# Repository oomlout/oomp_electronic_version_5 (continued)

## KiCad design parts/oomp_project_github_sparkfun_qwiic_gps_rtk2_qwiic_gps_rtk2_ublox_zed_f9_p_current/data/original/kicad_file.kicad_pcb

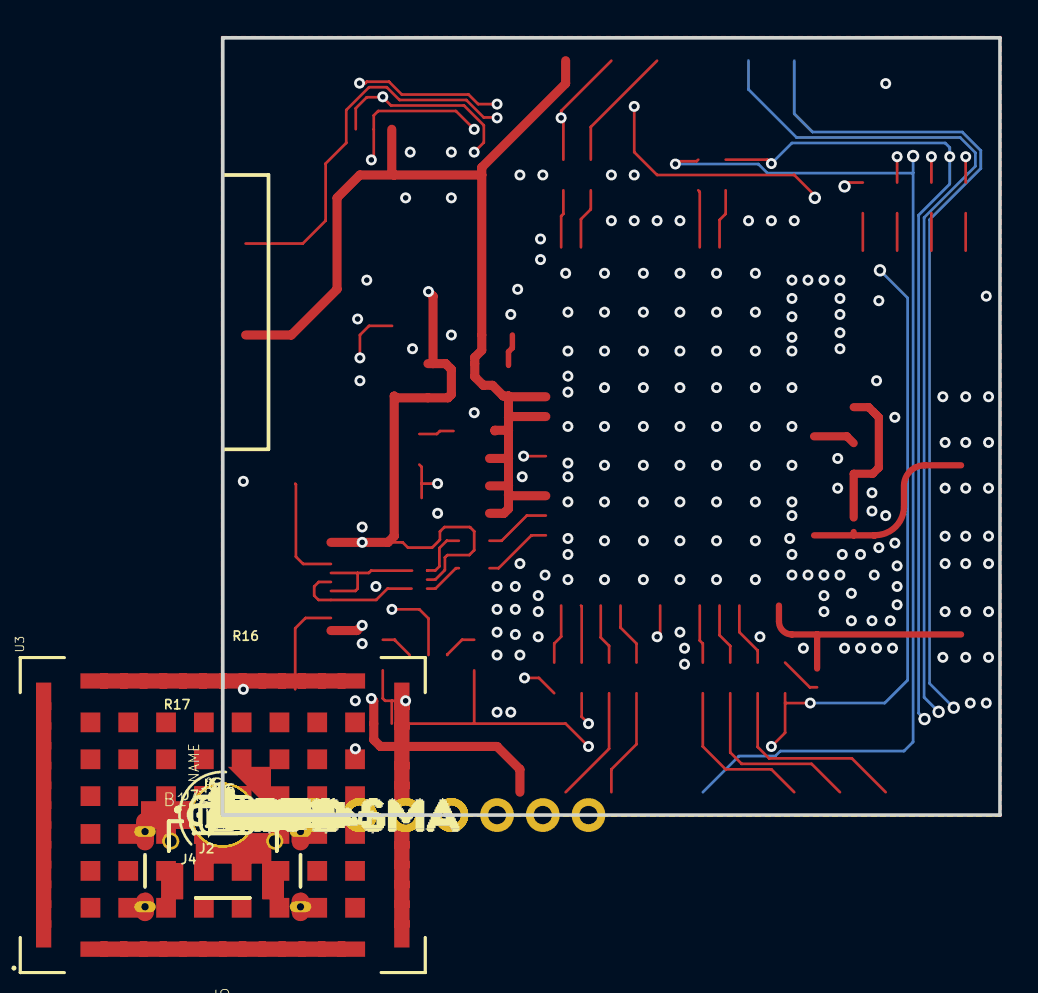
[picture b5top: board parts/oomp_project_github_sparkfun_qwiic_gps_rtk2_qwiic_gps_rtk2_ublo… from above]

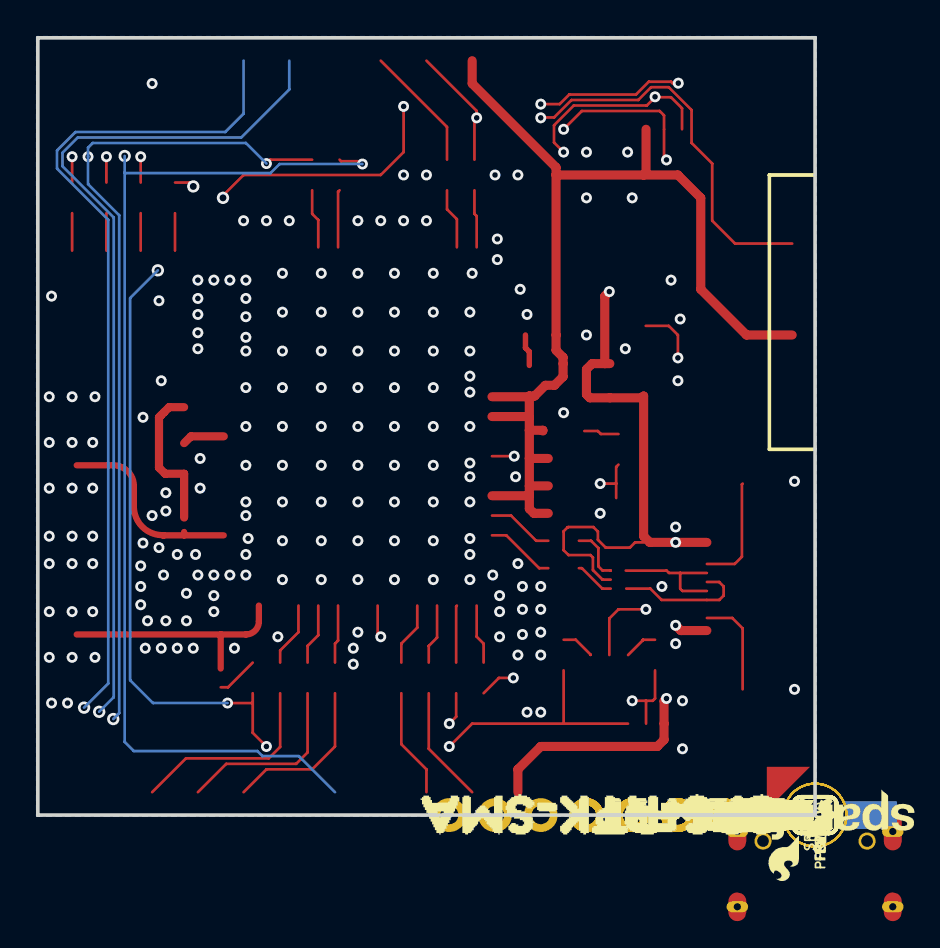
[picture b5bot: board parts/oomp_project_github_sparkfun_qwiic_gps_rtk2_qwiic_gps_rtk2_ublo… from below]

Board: 4 copper layers, 43.2 x 43.2 mm, 143 parts (44 on the bottom side), 52 nets.

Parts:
B1: 6.8MM_COIN_CELL; ML414H_IV01E
C1: 47pF; 0402
C2, C3, C4, C6: 1.0uF; 0603
C5, C7: 0.1uF; 0603
D1: Yellow; LED-0603
D2: 0.5A/40V/420mV; SOD-323
D3: GREEN; LED-0603
D4: BLUE; LED-0603
D6: PRTR5V0U2F; SOT886
E1, E2: SMA; SMA-EDGE
FB1: 120NH; 0402_MURATA
FENCE0: SMT-JUMPER_2_NC_TRACE_SILK
FRAME2: FRAME-LEDGER; CREATIVE_COMMONS
J1: Radio; 1X06_NO_SILK
J2, J4: Qwiic Right Angle; JST04_1MM_RA
J3: PTH; 1X04_NO_SILK
J5: USB-C-16P-2LAYER-PADS
J6: 1X06_NO_SILK
J7: 1X09_NO_SILK
JP5: SMT-JUMPER_3_2-NC_TRACE_SILK
JP21, JP61, JP71, JP81: FIDUCIALUFIDUCIAL; MICRO-FIDUCIAL
JP31, JP41, JP91, JP101: STAND-OFF
LED2: RED; LED-0603
LOGO1: OSHW-LOGOMINI; OSHW-LOGO-MINI
LOGO2: SFE_LOGO_NAME_FLAME.1_INCH; SFE_LOGO_NAME_FLAME_.1
PPS0: SMT-JUMPER_2_NC_TRACE_SILK
PPS_LED0: SMT-JUMPER_2_NC_TRACE_SILK
PWR0: SMT-JUMPER_2_NC_TRACE_SILK
R1, R5, R11, R12, R13: 1k; 0603
R2, R3, R4, R6, R14, R18, R19, R20, R21, R22, R23, R24, R25: 33; 0603
R7, R8: 2.2k; 0603
R9, R10: 27; 0603
R15: 100k; 0603
R16, R17: 5.1k; 0603
RTK0: SMT-JUMPER_2_NC_TRACE_SILK
SPI0: SMT-JUMPER_2_NO_SILK
U2: 3.3V; SOT23-5
U3: ZED-F9P
U$1, U$4: SDA-[)
U$2: SPECIAL_INSTRUCTIONS-ORDERING; ORDERING_INSTRUCTIONS
U$3, U$5: SCL-[)
U$6, U$7, U$60, U$61, U$66, U$67: 3V3-04
U$8, U$9, U$62, U$63: GND-04
U$10: I_SUPER2_C-()-03
U$11, U$54: FENCE2
U$12, U$18: PWR-()-03
U$13, U$28, U$29, U$32: RTK1
U$14, U$17: FENCE0
U$15, U$16: INT8
U$19, U$20: 5V
U$21, U$56, U$58: RX20
U$22: U#BLOX3
U$23, U$24: CS#-_]
U$25, U$52, U$72: PPS0
U$26, U$31: RX#MOSI3
U$27: DSEL0
U$30: QWIIC_4MM
U$33: SFE_LOGO_FLAME_.1
U$34, U$37: TX#MISO1
U$35, U$36: #RST3
U$38, U$41: SCK-(]-04
U$39, U$40: #SAFE1
U$42: RX22
U$43, U$44: PPS5
U$45, U$68: GND3
U$47, U$74: PPS1
U$48, U$70: RTCM5
U$49: ZED#F9P6
U$50, U$55, U$57: TX21
U$51: TX23
U$53, U$69: CORRECTION0
U$59: GPS0
U$65: ACTIVE_L1#L21
U$71, U$75: ANTENNA2
U$73: RTK#SMA4
U$76: GPS#RTK#SMA5

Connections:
3.3V: C2.1, C4.1, C5.2, C7.2, D2.A, J1.4, J2.2, J3.2, J4.2, J7.7, JP5.2, PWR0.2, R15.2, U2.5, U3.33, U3.34, U3.38
5V: C6.1, D6.5, J5.VBUS1, J5.VBUS2, J7.8, U2.1, U2.3
ANT_VCC: C1.1, FB1.P2, R14.1
BACKUP: B1.+, C3.1, R5.1, U3.36
CC1: J5.A5, R17.2
CC2: J5.B5, R16.2
D+: D6.4, R9.1
D-: D6.6, R10.1
D_SEL: SPI0.2, U3.47
FENCE_STAT: FENCE0.2, J6.1, R25.2
GND: B1.-, C1.2, C2.2, C3.2, C4.2, C5.1, C6.2, C7.1, D1.C, D3.C, D4.C, D6.2, E1.GND@0, E1.GND@1, E1.GND@2, E1.GND@3, E2.GND@0, E2.GND@1, E2.GND@2, E2.GND@3, J1.6, J2.1, J3.1, J4.1, J5.GND, J5.GND2, J5.SHLD1, J5.SHLD2, J5.SHLD3, J5.SHLD4, J7.9, LED2.C, R15.1, R16.1, R17.1, SPI0.1, U2.2, U3.1, U3.3, U3.12, U3.14, U3.32, U3.37, U3.41, U3.48, U3.55, U3.56, U3.57, U3.58, U3.59, U3.60, U3.61, U3.62, U3.63, U3.64, U3.65, U3.66, U3.67, U3.68, U3.69, U3.70, U3.71, U3.72, U3.73, U3.74, U3.75, U3.76, U3.77, U3.78, U3.79, U3.80, U3.81, U3.82, U3.83, U3.84, U3.85, U3.86, U3.87, U3.88, U3.89, U3.90, U3.91, U3.92, U3.93, U3.94, U3.95, U3.96, U3.97, U3.98, U3.99, U3.100, U3.101, U3.102
GPS_ANT1: E1.SIG, FB1.P1, U3.2
INT: J6.6, R18.2
unnamed: D3.A, R12.1
unnamed: D1.A, R11.1
unnamed: R12.2, RTK0.1
unnamed: PPS_LED0.1, R11.2
unnamed: JP5.1, R8.2
unnamed: D2.C, R5.2
unnamed: D4.A, R13.1
unnamed: JP5.3, R7.2
unnamed: FENCE0.1, R13.2
unnamed: LED2.A, R1.1
unnamed: R9.2, U3.40
unnamed: R10.2, U3.39
unnamed: R14.2, U3.7
unnamed: R22.1, U3.26
unnamed: R18.1, U3.51
unnamed: R19.1, U3.49
unnamed: PWR0.1, R1.2
unnamed: R20.1, U3.50
unnamed: R24.1, U3.20
unnamed: R25.1, U3.19
unnamed: PPS0.1, R21.1
PPS: E2.SIG, PPS0.2, U3.53
PPS_STAT: J6.3, PPS_LED0.2, R21.2
RTK_STAT: J6.2, R24.2, RTK0.2
RX2: J1.3, J7.5, R22.2
RXI/MOSI: J7.3, R6.2
RXLV: R6.1, U3.43
SCL/SCK: J2.4, J3.4, J4.4, J7.1, R4.2, R7.1
SCL_LV: R4.1, U3.45
SDA/~CS: J2.3, J3.3, J4.3, J7.4, R2.2, R8.1
SDA_LV: R2.1, U3.44
TX2: J1.2, J7.6, R23.2
TX2_P: R23.1, U3.27
TXLV: R3.1, U3.42
TXO/MISO: J7.2, R3.2
UNP_D+: D6.3, J5.A6, J5.B6
UNP_D-: D6.1, J5.A7, J5.B7
~RESET: J6.4, R19.2
~SAFE: J6.5, R20.2

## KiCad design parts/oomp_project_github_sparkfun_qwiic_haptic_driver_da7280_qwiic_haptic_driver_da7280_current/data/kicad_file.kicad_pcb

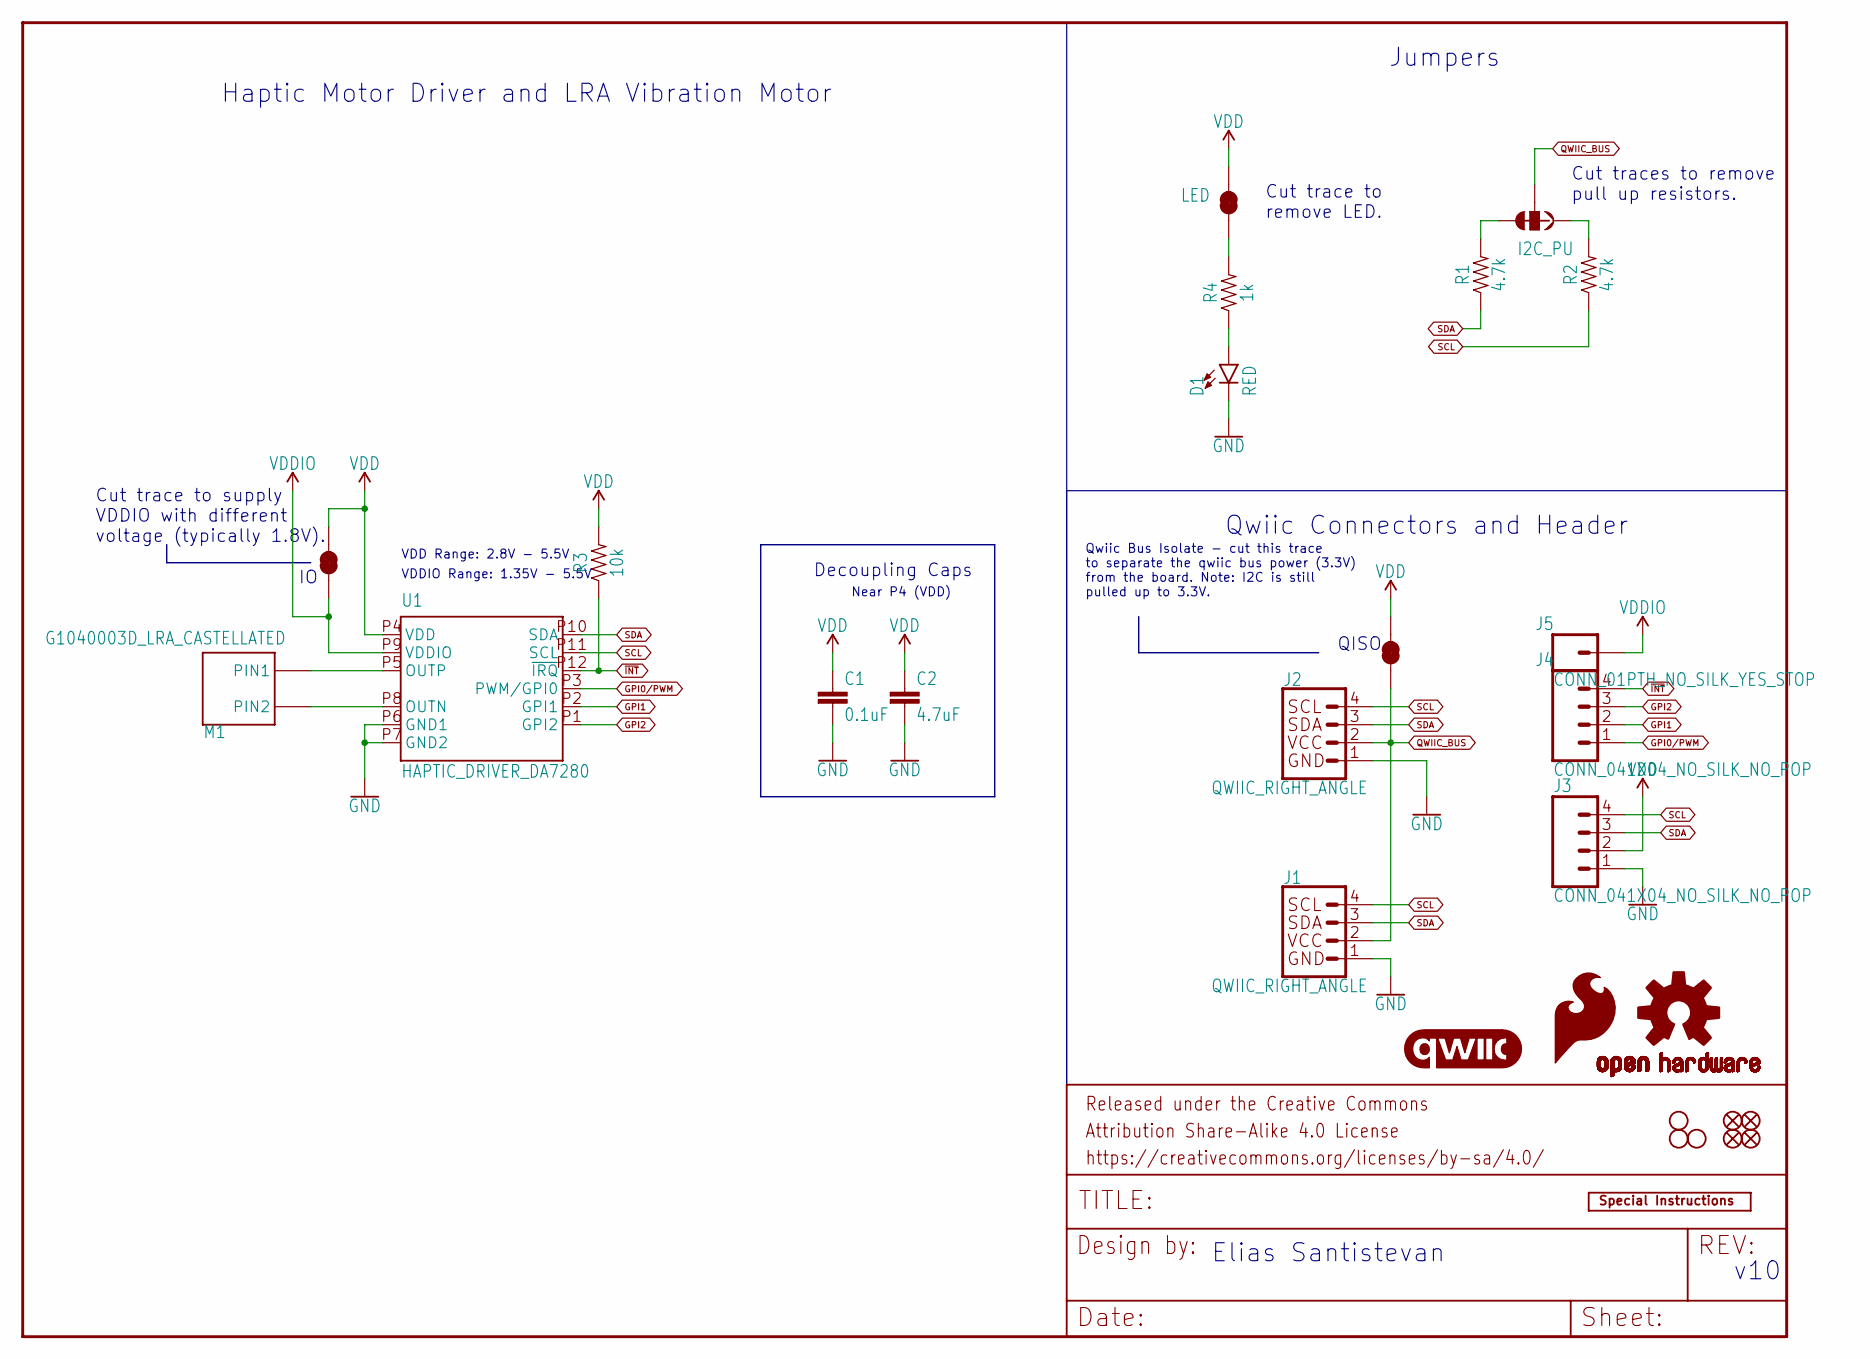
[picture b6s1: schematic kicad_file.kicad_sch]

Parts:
C1: 0.1uF; 0603
C2: 4.7uF; 0603
D1: RED; LED-0603
FD1, FD2, FD3, FD4: FIDUCIALUFIDUCIAL; FIDUCIAL-MICRO
FRAME1: FRAME-LETTER; CREATIVE_COMMONS
H1, H2, H4: STAND-OFFTIGHT; STAND-OFF-TIGHT
J1, J2: QWIIC_RIGHT_ANGLE; JST04_1MM_RA
J3, J4: CONN_041X04_NO_SILK_NO_POP; 1X04_NO_SILK
J5: CONN_01PTH_NO_SILK_YES_STOP; 1X01_NO_SILK
JP1, JP2, JP4: LED; SMT-JUMPER_2_NC_TRACE_SILK
JP3: I2C_PU; SMT-JUMPER_3_2-NC_TRACE_SILK
LOGO1: SPECIAL_INSTRUCTIONS-ORDERING; ORDERING_INSTRUCTIONS
LOGO2: OSHW-LOGOS; OSHW-LOGO-S
LOGO4: SFE_LOGO_FLAME.1_INCH; SFE_LOGO_FLAME_.1
M1: G1040003D_LRA_CASTELLATED; COIN_VIBRATION_MOTOR_CASTEL
R1, R2: 4.7k; 0603
R3: 10k; 0603
R4: 1k; 0603
U1: HAPTIC_DRIVER_DA7280; QFN_DA7280
U$1: QWIIC_LOGO_3MM; QWIIC_3MM

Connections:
GND: C1.2, C2.2, D1.C, J1.1, J2.1, J3.1, U1.P6 (GND1), U1.P7 (GND2)
GPI0/PWM: J4.1, U1.P3 (PWM/GPI0)
GPI1: J4.2, U1.P2 (GPI1)
GPI2: J4.3, U1.P1 (GPI2)
unnamed: D1.A, R4.1
unnamed: JP1.1, R4.2
unnamed: JP3.3, R1.2
unnamed: JP3.1, R2.2
unnamed: M1.P$1 (PIN1), U1.P5 (OUTP)
unnamed: M1.P$2 (PIN2), U1.P8 (OUTN)
QWIIC_BUS: J1.2, J2.2, JP3.2, JP4.1
SCL: J1.4, J2.4, J3.4, R2.1, U1.P11 (SCL)
SDA: J1.3, J2.3, J3.3, R1.1, U1.P10 (SDA)
VDD: C1.1, C2.1, J3.2, JP1.2, JP2.2, JP4.2, R3.2, U1.P4 (VDD)
VDDIO: J5.1, JP2.1, U1.P9 (VDDIO)
~INT: J4.4, R3.1, U1.P12 (~IRQ)

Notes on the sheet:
v10
Qwiic Connectors and Header
Cut trace to supply VDDIO with different voltage (typically 1.8V).
Haptic Motor Driver and LRA Vibration Motor
VDDIO Range: 1.35V - 5.5V
Jumpers
Near P4 (VDD)
Elias Santistevan
QISO
Cut trace to remove LED.
Decoupling Caps
Qwiic Bus Isolate - cut this trace to separate the qwiic bus power (3.3V) from the board. Note: I2C is still pulled up to 3.3V.
VDD Range: 2.8V - 5.5V
Cut traces to remove pull up resistors.

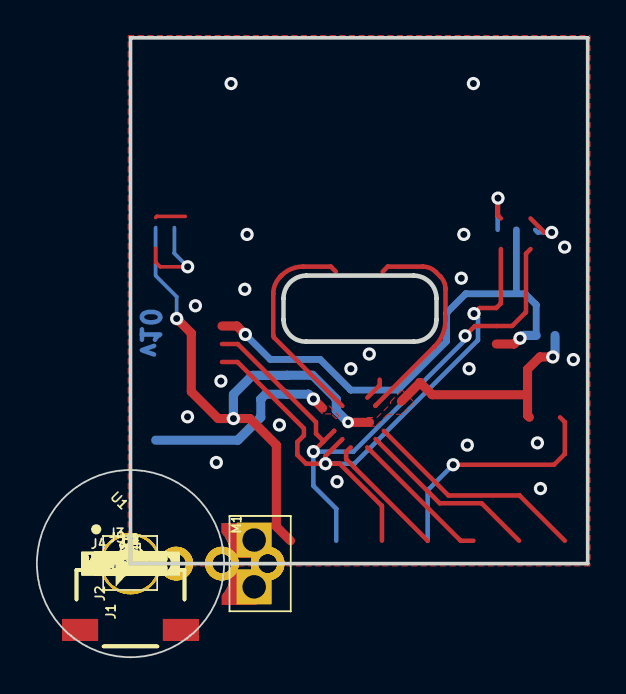
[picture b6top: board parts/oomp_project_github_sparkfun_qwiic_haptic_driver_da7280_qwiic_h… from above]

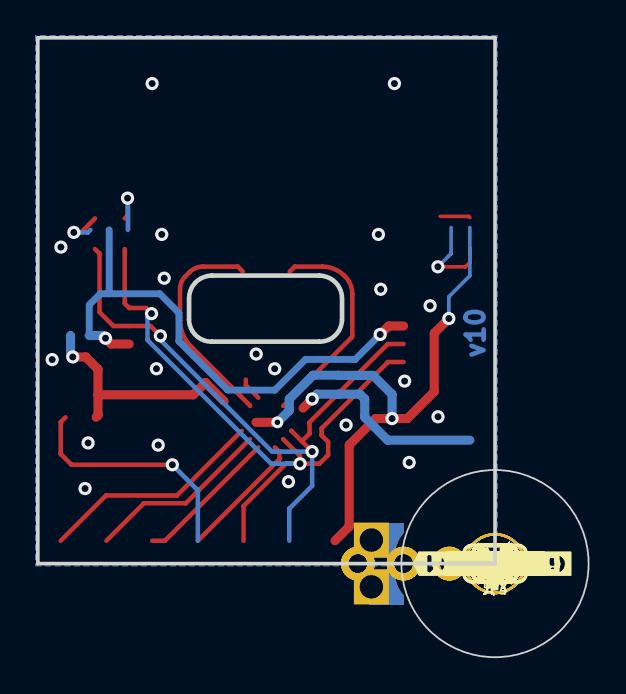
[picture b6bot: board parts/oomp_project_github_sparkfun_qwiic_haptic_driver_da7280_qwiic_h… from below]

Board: 2 copper layers, 30.6 x 34.4 mm, 58 parts (25 on the bottom side), 16 nets.

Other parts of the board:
U$2: #3V3#1
U$3, U$18: #GND#0
U$4: #GPI0#6
U$5: #GPI1#6
U$6: #GPI2#6
U$7: #VDD#4
U$8: #SDA#4
U$9: HAPTIC6
U$10: MOTOR7
U$11: DRIVER8
U$12: #GPI0#PWM#2
U$13: #GPI1#2
U$14: #GPI2#2
U$15, U$25: #VDDIO#5
U$16: #SDA#0
U$19: #SCL#5
U$20: PWR72810
U$21: #SCL#1
U$23: #I2C#4
U$24: #LED#4
U$26: SFE_LOGO_FLAME_.1
U$27: ##INT##3
U$28: ##INT##6
U$29: DA72809
U$30: #IO#6
U$31: #QISO#0

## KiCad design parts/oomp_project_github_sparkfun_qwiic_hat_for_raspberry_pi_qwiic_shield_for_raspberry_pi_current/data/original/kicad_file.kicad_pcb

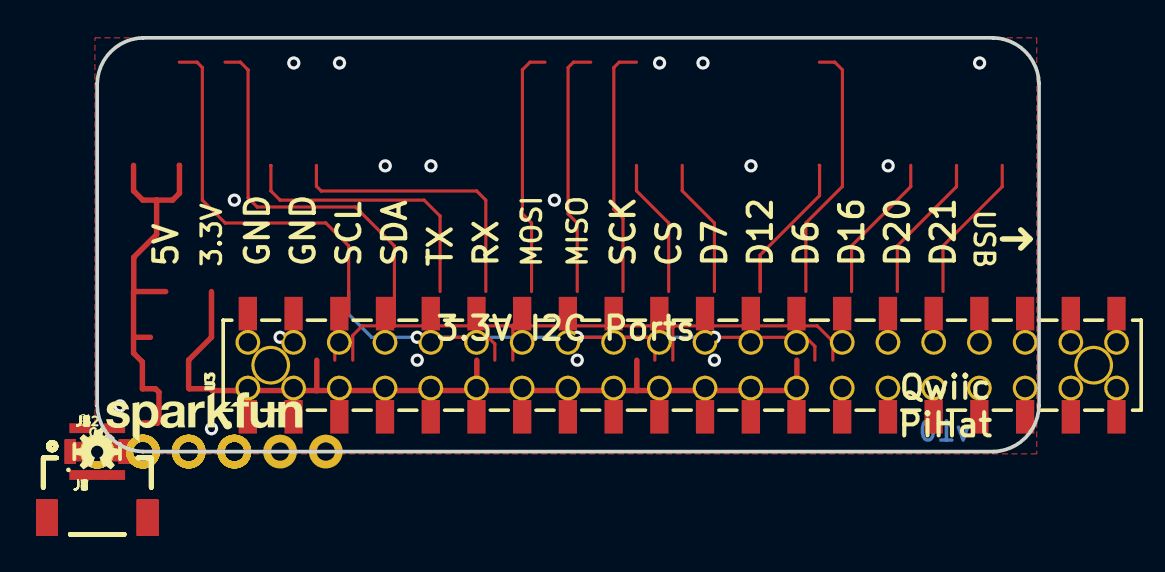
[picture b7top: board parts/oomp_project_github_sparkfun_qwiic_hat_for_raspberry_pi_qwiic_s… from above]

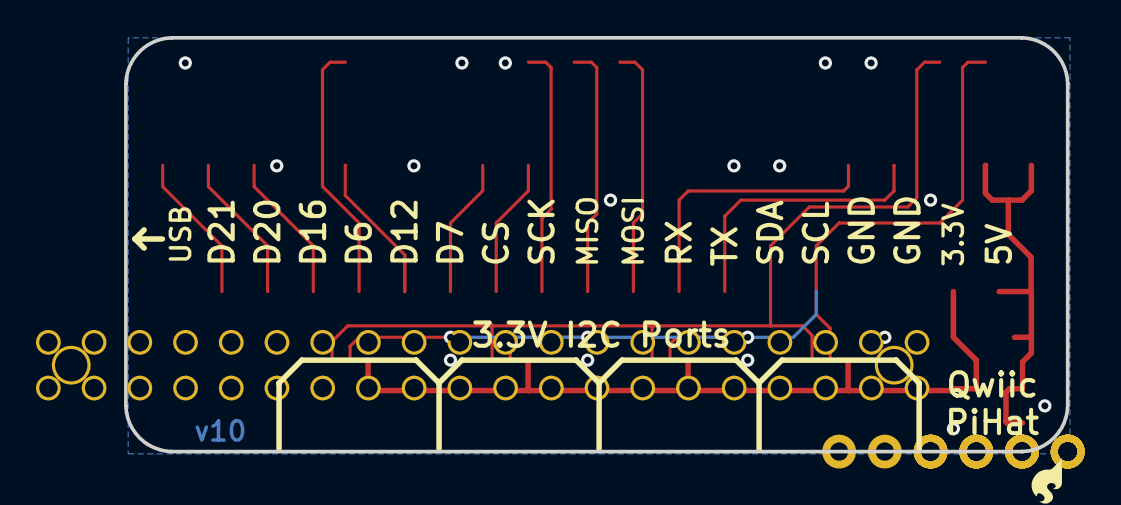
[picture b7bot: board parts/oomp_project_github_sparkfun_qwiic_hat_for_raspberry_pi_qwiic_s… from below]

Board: 2 copper layers, 52.3 x 23.0 mm, 22 parts (3 on the bottom side), 17 nets.

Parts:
C1, C3: 1.0uF; 0603
FD1, FD2, FD3, FD4: FIDUCIAL1X2; FIDUCIAL-1X2
FRAME1: FRAME-LETTER; CREATIVE_COMMONS
J1, J6, J7, J8: Qwiic Right Angle; 1X04_1MM_RA
J2, J12: 1X02_NO_SILK
J3, J5: 1X04_NO_SILK
J4: 1X06_NO_SILK
LOGO1: OSHW-LOGOMINI; OSHW-LOGO-MINI
LOGO2: REVISION
U2: 3.3V/600mA; SOT23-5
U3: RASPBERRY_PI_SHIELD_BOTTOM_ENTRY_NOHOLES
U$1: SFE_LOGO_FLAME.1_INCH; SFE_LOGO_FLAME_.1
U$2: SFE_LOGO_NAME.1_INCH; SFE_LOGO_NAME_.1

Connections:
3.3V: C3.1, J1.2, J5.2, J6.2, J7.2, J8.2, U2.5
5V: C1.1, J5.1, U2.1, U2.3, U3.2, U3.4
CS: J3.4, U3.24
D6: J4.3, U3.31
D7: J4.1, U3.26
D12: J4.2, U3.32
D16: J4.4, U3.36
D20: J4.5, U3.38
D21: J4.6, U3.40
GND: C1.2, C3.2, J1.1, J5.3, J5.4, J6.1, J7.1, J8.1, U2.2, U3.6, U3.9, U3.14, U3.20, U3.25, U3.30, U3.34, U3.39
MISO: J3.2, U3.21
MOSI: J3.1, U3.19
RX: J2.2, U3.10
SCK: J3.3, U3.23
SCL: J1.4, J6.4, J7.4, J8.4, J12.2, U3.5
SDA: J1.3, J6.3, J7.3, J8.3, J12.1, U3.3
TX: J2.1, U3.8

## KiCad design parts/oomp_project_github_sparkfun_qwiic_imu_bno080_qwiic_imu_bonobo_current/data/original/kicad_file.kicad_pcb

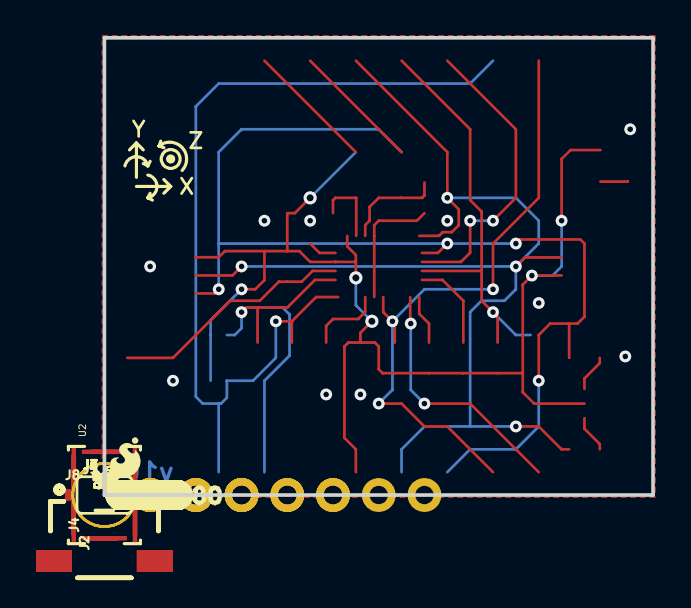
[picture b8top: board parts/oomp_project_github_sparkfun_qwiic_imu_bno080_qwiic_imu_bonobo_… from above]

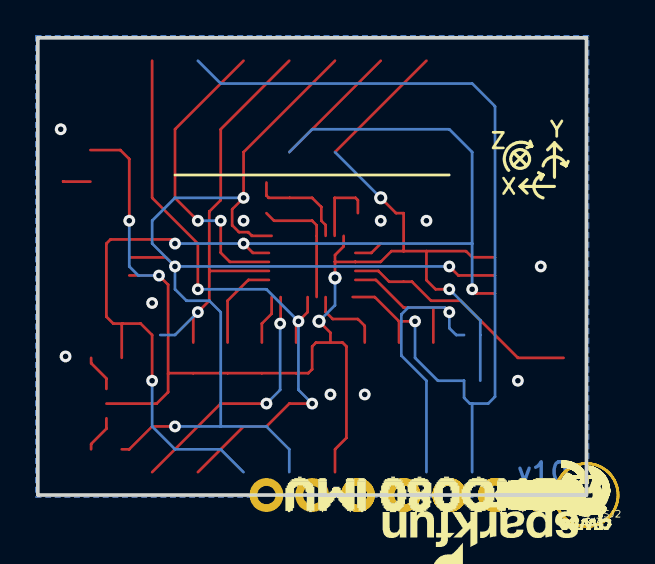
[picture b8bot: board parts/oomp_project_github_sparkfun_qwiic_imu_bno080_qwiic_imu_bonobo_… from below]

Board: 2 copper layers, 30.5 x 25.4 mm, 89 parts (35 on the bottom side), 19 nets.

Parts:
C1, C2, C4: 0.1uF; 0603
C3, C5: 22pF; 0603
D1: RED; LED-0603
FRAME1: FRAME-LETTER; CREATIVE_COMMONS
J1: 1X06_NO_SILK
J2, J4: SMD; 1X04_1MM_RA
J3: PTH; 1X04_NO_SILK
J5: 1X01_NO_SILK
J6: SPI; 1X08_NO_SILK
J7, J8: 1X02_NO_SILK
JP1, JP2, JP5, JP6: FIDUCIALUFIDUCIAL; MICRO-FIDUCIAL
JP3, JP4: STAND-OFF
LOGO1: OSHW-LOGOMINI; OSHW-LOGO-MINI
LOGO2: REVISION
LOGO4: SFE_LOGO_FLAME.1_INCH; SFE_LOGO_FLAME_.1
LOGO5: SFE_LOGO_NAME_FLAME.1_INCH; SFE_LOGO_NAME_FLAME_.1
R1, R3, R6, R7, R8: 10k; 0603
R2: 1k; 0603
R9, R10: 4.7k; 0603
R12, R13: 2.2k; 0603
SJ1: SMT-JUMPER_3_2-NC_PASTE_SILK
SJ2, SJ3, SJ4: SJ_2S-NO
U2: BNO080; LGA-28
U$1: (PWR)
U$2: BOOT2
U$3, U$4: #RST_
U$5, U$6: SCL
U$7, U$8: SDA
U$9, U$10: 3V3
U$11, U$50: 3V30
U$12, U$13: SCK0
U$14: PS03
U$15, U$16: GND
U$17, U$18: SI1
U$19, U$20: #WAK6
U$21: 3V32
U$22: RXI1
U$23: (I_SUPER2_C)
U$25, U$26: #INT0
U$27, U$28: PS14
U$29: PS05
U$30: ADR0
U$33: PS114
U$34: PS015
U$35: TXO0
U$39: UART8
U$40: GRN10
U$41: BLK9
U$42, U$43: GND1
U$44: BNO080_IMU11
U$46: BNO08012
U$47: IMU13
U$49, U$51: #RST7
U$52, U$53: #CS3
U$54, U$55: SO0
U$59: QWIIC#LABEL#FULL#M#PNG
Y1: 32.768kHz; CRYSTAL-SMD-3.2X1.5MM

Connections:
3.3V: C2.1, C4.1, D1.A, J1.3, J2.2, J3.2, J4.2, J6.2, R1.2, R3.2, R6.2, R9.2, R10.2, SJ1.2, SJ3.1, SJ4.1, U2.3, U2.28
ADDR/MOSI: J6.5, R3.1, SJ2.2, U2.17
CAP: C1.1, U2.9
GND: C1.2, C2.2, C3.2, C4.2, C5.2, J1.1, J2.1, J3.1, J4.1, J6.1, R2.1, R7.1, R8.1, SJ2.1, U2.2, U2.10, U2.25
unnamed: C5.1, U2.27, Y1.P$2
unnamed: C3.1, U2.26, Y1.P$1
unnamed: D1.C, R2.2
PS0/WAKE: J6.7, J8.2, R7.2, SJ3.2, U2.6
PS1: J8.1, R8.2, SJ4.2, U2.5
SCL/SCK/RX: J1.4, J2.4, J3.4, J4.4, J6.3, R12.1, U2.19
SCL_PU: R12.2, SJ1.1
SDA/MISO/TX: J1.5, J2.3, J3.3, J4.3, J6.4, R13.1, U2.20
SDA_PU: R13.2, SJ1.3
S_SCL: R10.1, U2.15
S_SDA: R9.1, U2.16
~BOOT: J5.1, R6.1, U2.4
~CS: J6.6, U2.18
~INT: J7.2, U2.14
~RST: J6.8, J7.1, R1.1, U2.11
